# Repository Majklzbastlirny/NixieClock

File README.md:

# NixieClock (ESP-IDF firmware)

ESP-IDF + PlatformIO firmware for a 6-tube multiplexed nixie clock, replacing
the original ESPHome config (`nixieclock.yaml`, kept for reference). WiFi is used
for time sync and remote control; the clock keeps running (and keeps time, via
its RTC) with no network.

> **New here?** See **[GUIDE.md](GUIDE.md)** — a bilingual (English / Čeština)
> user guide with a *For everyone* section (setup, buttons, web page) and a
> *Power users* section (REST, MQTT/Home Assistant, building the firmware).

## Hardware

ESP32 (WROOM-32) on the **UCB32** controller board driving the
[**Unidisp**](https://github.com/Unipuls80/Unidisp) display board:

- Onboard UC3845 HV supply (~180 V, **no dimming input** → brightness is done in
  firmware by PWM-ing each tube's anode within its multiplex slot — the headline
  feature that wasn't possible under ESPHome).
- **MH74141** BCD cathode driver (old/slow Tesla part), **74×42** 1-of-10 anode
  multiplexer, 6× Z57xM/ZM1080 tubes. No per-digit decimal points — the only
  separator is the colon between the MM:SS pair.
- **PCF8563** RTC @ I²C 0x51 (driver also auto-detects DS1307/DS3231 @ 0x68).
- 5 front buttons on the multiplexed KEY line + a dedicated snooze button.
- Passive piezo buzzer on the ALM line (LEDC tone / RTTTL).
- Up to 2× **DS18B20** 1-Wire temperature sensors on GPIO13 (needs a 4.7 kΩ
  pull-up to 3.3 V).
- Optional **BH1750** ambient-light sensor on the shared I²C bus (address 0x23 or
  0x5C) — auto-detected at boot; enables light-driven night dimming when fitted.

Full pin map: [`components/common/include/pins.h`](components/common/include/pins.h).
Printable enclosure (case, bezel, panels, TPU feet) + print/assembly notes:
[`3D_Files/`](3D_Files/).

## Build & flash

Requires [PlatformIO](https://platformio.org/install) (CLI or the VS Code ext).

```sh
pio run                 # build
pio run -t upload       # build + flash over USB
pio device monitor      # serial console @ 115200
```

PlatformIO downloads the ESP-IDF 5.5 toolchain and the managed components
(`espressif/onewire_bus`, `espressif/ds18b20`) automatically on first build.
After changing a component's `idf_component.yml` or `REQUIRES`, do a clean
configure (`rm -rf .pio/build/esp32dev`) so the component manager re-runs.

> The board has **no auto-reset**: hold IO0, tap EN, release IO0 to enter
> download mode before `pio run -t upload`.

### Over-the-air (OTA) updates

The flash is a dual-OTA layout (two ~1.875 MB app slots + `otadata`), so after the
**first** serial flash you can update firmware over WiFi and never cable the clock
again:

1. `pio run` to build a new `.pio/build/esp32dev/firmware.bin`.
2. Open the clock's web UI (its IP is shown at the top of the page) → **Firmware**
   section → pick that `firmware.bin` → **Upload**.
3. It streams into the spare slot and reboots into it. The **Running** line shows the
   version and active slot (`ota_0`/`ota_1`), which flips after each successful update.

A failed or interrupted upload leaves the current firmware bootable — the new slot is
only made active once the whole image is written and verified. Settings and
WiFi/MQTT credentials live in NVS and are untouched by updates.

## First-time setup / credentials

Credentials live in NVS (set via the SoftAP portal or the web UI).
`components/common/include/secrets.h` (gitignored) is a **first-boot fallback
only**: once a WiFi SSID is stored in NVS the device trusts NVS exclusively (an
empty MQTT host means *no MQTT* — the client goes idle), and a factory reset
forces SoftAP setup on the next boot regardless of `secrets.h`.

To seed defaults at compile time, copy the template:

```sh
cp components/common/include/secrets.example.h components/common/include/secrets.h
# edit WIFI_SSID / WIFI_PASS / MQTT_* 
```

Or skip `secrets.h` entirely and provision over WiFi (see below).

## WiFi provisioning (SoftAP)

To set credentials without editing code (e.g. when lending the clock):

1. **Enter provisioning** — hold the provision button (button 5) during the
   boot window, or long-hold it (~3 s) during normal operation; it reboots into
   setup mode. (A board with no stored creds and no fallback SSID enters it
   automatically.)
2. The tubes show an **8-digit PIN** in two halves (colon lit = first half).
   Join the open-looking `NixieClock-XXXXXX` WiFi using that PIN as the WPA2
   password — so only someone looking at the clock can connect.
3. A captive portal opens: pick your network, enter the password (and optionally
   MQTT settings), save. The clock stores the creds and reboots onto your LAN.

WiFi/MQTT can also be changed live from the web UI's **Network** section (MQTT
applies immediately; WiFi on next reboot).

## Buttons

| Button | Short press | Long hold |
|--------|-------------|-----------|
| 1 | Brightness up | — |
| 2 | Brightness down | — |
| 3 | Show temperature now | — |
| 4 | Anti-poison scrub now | — |
| 5 (provision) | Show IP address on tubes | ~3 s: provisioning · ~10 s: factory reset |
| Snooze | Snooze ringing alarm | Dismiss alarm (until tomorrow) |

Bonus combo: **hold brightness + and − together (~2 s)** toggles the alarm on/off.

## Control surfaces

All three share one settings store, so changes from any surface are reflected
everywhere instantly:

- **Web UI** — `http://<clock-ip>/` : brightness, night schedule, anti-poison
  (interval, length, speed, 5 animations + mix, pause-for-interludes),
  alarm (incl. day-of-week + melody + snooze), temperature slots/decimals, and
  network config. Tap button 5 to see the IP on the tubes.
- **MQTT + Home Assistant** — auto-discovers as a *Nixie Clock* device
  (`nixie-<mac>`). Topics under `nixieclock/<node>/…`, HA discovery under
  `homeassistant/…`.
- **REST/JSON** — `GET /api/state`, `POST /api/set?k=<key>` (value in body) or
  the `GET /api/set?k=…&v=…` alias, `POST|GET /api/action?a=<action>`,
  `GET|POST /api/settime?epoch=…&tz=…` (set the clock from a client),
  `GET /api/net`, `POST /api/netset`, `POST /api/ota` (firmware upload),
  `GET /api/log`, `GET /api/blescan`, `GET /api/shellytime`.

## Features

- Smooth multiplex PWM brightness, ghost-free (cathode-before-anode + dead-time).
- SNTP timekeeping (configurable POSIX timezone), seeded from and written back to
  the RTC. Off-grid you can **set the clock from a phone/PC** — the web page and
  the SoftAP setup portal both send the device's time (and timezone), no NTP
  needed. The time is also saved to flash every few hours, so a power-lost RTC
  boots to an approximate time instead of 1970.
- Optional **Shelly BLE time**: Gen2+ Shellies (fw 2.x) acting as BLE gateways
  broadcast a time beacon (the one the Shelly BLU H&T Display syncs from), which
  the existing BLE scan picks up.
  - **Sync from Shelly now** button (web / HA / `shelly_sync` action).
  - Optional **daily** sync (`shelly_time_daily`), which yields to NTP: it only
    acts when SNTP hasn't synced for 24 h.
  - Takes the median of the Shellies heard, compensated for their 0–3 s burst lag.
    Expect about ±1 s accuracy, because the beacon carries whole seconds.
  - Debug panel / `GET /api/shellytime` lists each sender with its offset from
    the clock.
- Manual brightness + night dimming with three selectable modes: a **fixed**
  clock-time window (default 20:30→06:00), **sunrise/sunset** computed on-device
  from a configurable lat/lon (fully offline — no network needed), or **ambient
  light** from an optional BH1750 sensor (auto-detected at boot on I²C 0x23/0x5C;
  the light-driven mode is offered only when the sensor is present).
- Anti-cathode-poisoning cycle (periodic + on-demand).
- Two temperature slots + a **date** shown as brief interludes near the end of
  each minute — each interlude's **start second and duration are configurable**
  (defaults temp1 :53, temp2 :55, date :57). Temps are fed by MQTT, a DS18B20, or
  a **Shelly BLU H&T** read directly over BLE (passive BTHome v2 scan — no
  hub/gateway/cloud, picked from a live list in the web UI; press the sensor's
  button to highlight it, and its battery level shows with a low-battery cue — a
  colon blink); a per-slot calibration offset (°C); configurable decimals;
  negatives shown by blinking (no minus glyph), colon as decimal point. The date
  reads `DDMM : DoW` (day, month, then the ISO weekday after the colon). Night
  dimming in sun mode also takes a twilight offset (stay bright longer into
  dusk/dawn).
- Alarm with snooze + dismiss, day-of-week mask, and RTTTL melodies.
- Cold-start "slot machine" animation until the time is known.
- **Over-the-air updates** — upload a new `firmware.bin` from the web UI (dual-OTA
  slots); no serial needed after the first flash.
- **Web log viewer** — recent device log over `GET /api/log`, since the assembled
  clock has no serial access.

## Project layout

```
platformio.ini             build config (env: esp32dev), custom partition table
partitions.csv             dual-OTA: 2x ~1.875 MB app slots + otadata + NVS + SPIFFS (4 MB flash)
sdkconfig.defaults         ESP-IDF defaults
src/main.c                 app entry: orchestration + display draw loop
components/
  common/                  shared pin map + secrets (header-only)
  nixie/                   GPTimer multiplex display driver + PWM brightness
  i2cbus/                  shared I²C master + bus scanner
  rtcdev/                  RTC driver (PCF8563 / DS1307 / DS3231 auto-detect)
  netclock/                WiFi STA + SNTP
  netcfg/                  WiFi/MQTT credential store (NVS + secrets fallback)
  provision/               SoftAP captive-portal WiFi provisioning
  settings/                persisted settings blob (NVS) + change versioning
  control/                 shared key=value apply + state-JSON core
  mqttctrl/                MQTT client + Home Assistant autodiscovery
  webui/                   self-hosted web UI + REST/JSON API
  temps/                   temperature slots + DS18B20 (RMT 1-Wire)
  blescan/                 NimBLE passive scan → Shelly BLU H&T (BTHome v2)
  shellytime/              Shelly BLE time beacon → optional clock sync
  bh1750/                  optional ambient-light sensor (I²C) for lux night mode
  weblog/                  esp_log → RAM ring buffer, read over /api/log
  buttons/                 multiplexed-button debounce + classification
  alarm/                   alarm state machine
  buzzer/                  LEDC tone + RTTTL player
  antipoison/              anti-cathode-poisoning routine
```

Architecture note: `control` is the single place that maps a setting key=value
and renders the state JSON; MQTT, the web UI, and REST all go through it, so
adding a setting touches one switch and one JSON builder, not three.

## License

This project uses reciprocal ("share-alike") open licenses — you may use, copy,
and modify it, including commercially, but you must publish your modifications to
whichever part you change:

- **Firmware / source code** — [GNU GPL v3](LICENSE) (`LICENSE` at the repo root).
- **UCB32 controller board** (`PCB_Sources/ucb vibecheck_final/`) —
  [CERN-OHL-S v2](PCB_Sources/ucb%20vibecheck_final/LICENSE.txt) (CERN Open
  Hardware Licence, Strongly Reciprocal).

Third-party content keeps its own license: the **Unidisp** display board
(`PCB_Sources/Unidisp-main/`) is licensed by its author under CERN-OHL-W (Weakly
Reciprocal) — see its bundled `LICENSE`. The original ESPHome reference
(`nixieclock.yaml`) is retained only for reference.

## Credits

This started as a university project. The **Unidisp** digitron display board —
the HV supply, multiplexing, and tube driving — is the work of
[**@Unipuls80**](https://github.com/Unipuls80), along with his original
[Unidisp](https://github.com/Unipuls80/Unidisp) and an
[MH106 ASIC-based controller (ucb106)](https://github.com/Unipuls80/ucb106).

The **UCB32** controller board and this ESP32 firmware are my "modern" take on
driving the same display — by **Michal Basler** ([@Majklzbastlirny](https://github.com/Majklzbastlirny)).

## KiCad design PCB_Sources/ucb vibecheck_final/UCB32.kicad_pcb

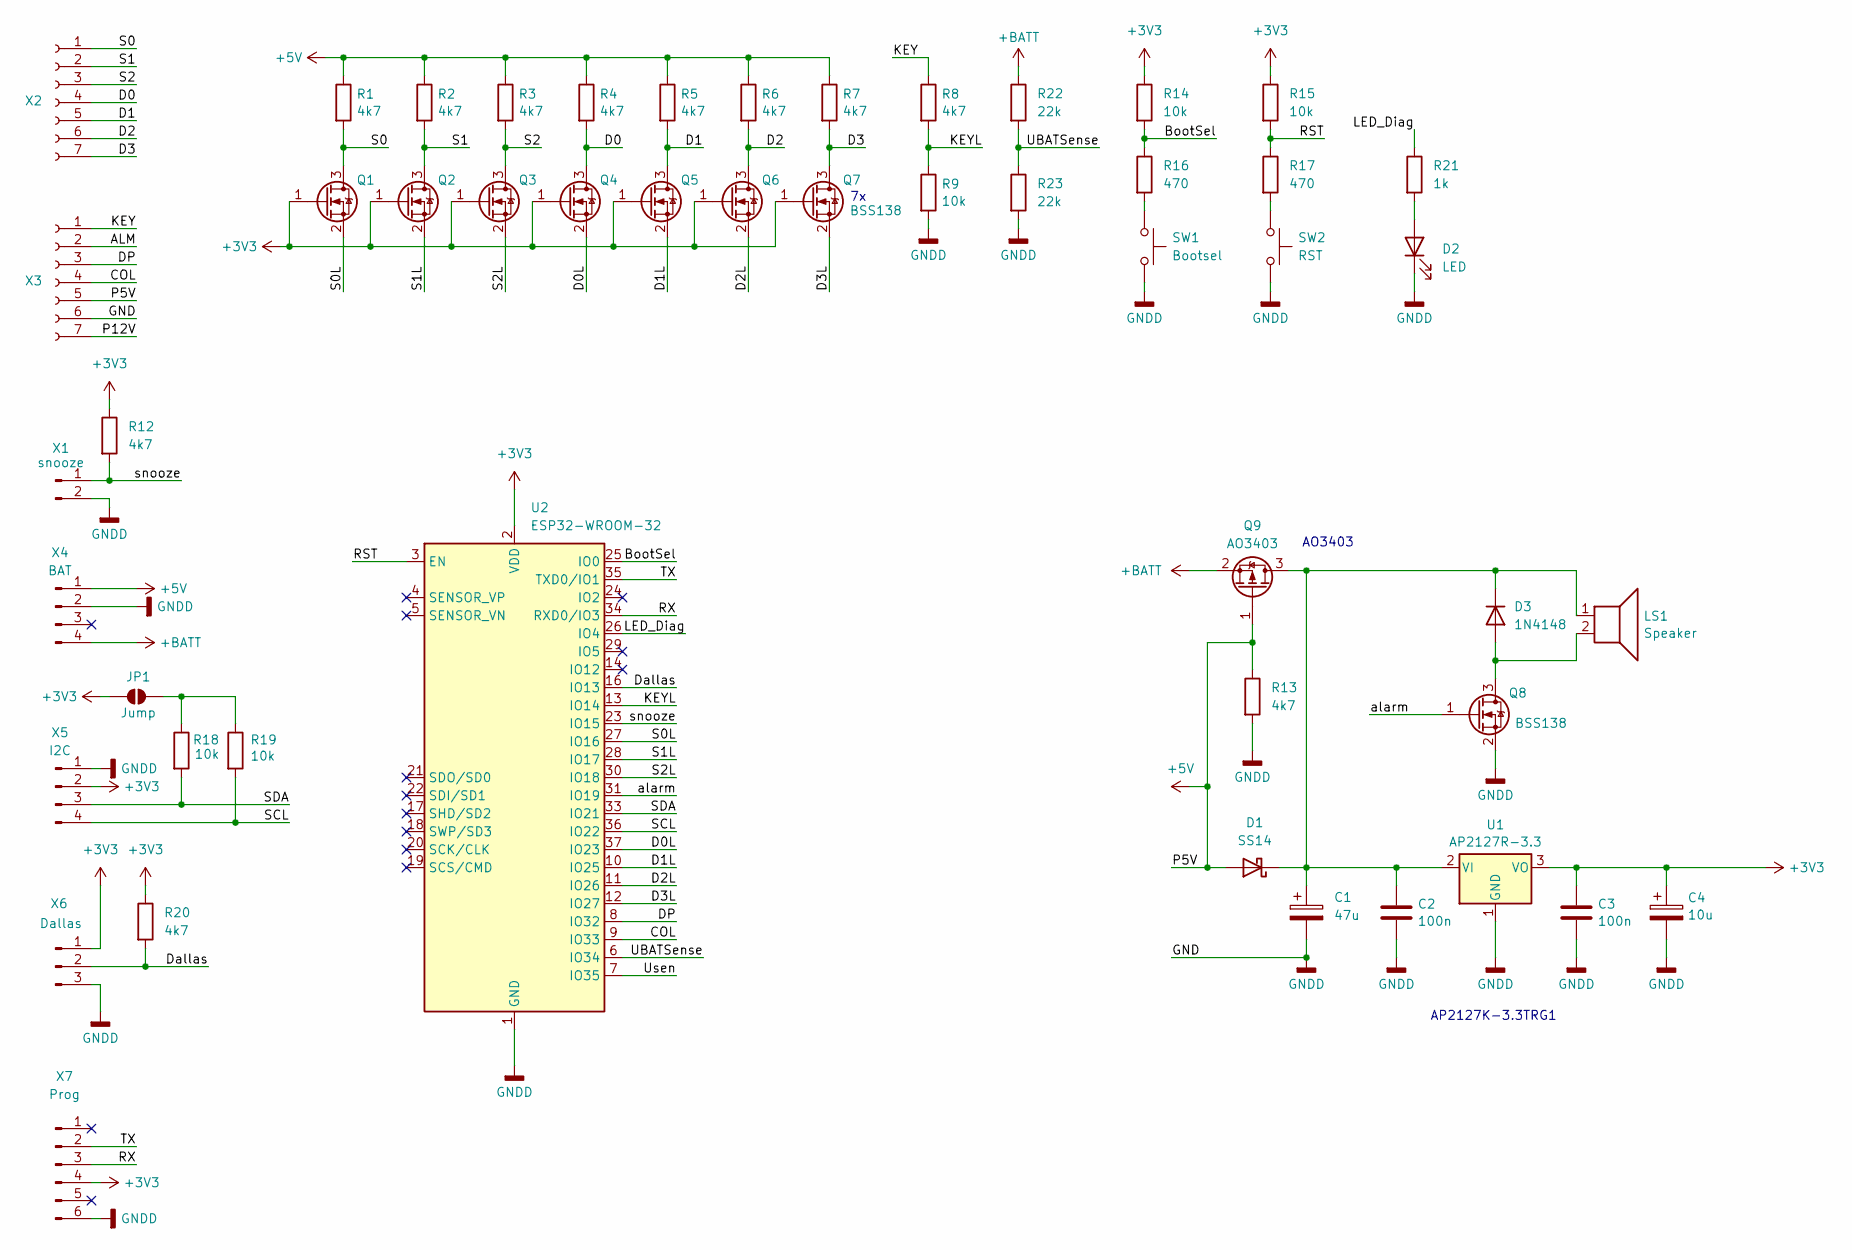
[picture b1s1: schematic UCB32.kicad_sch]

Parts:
C1: 47u; C_0805_2012Metric_Pad1.18x1.45mm_HandSolder
C2, C3: 100n; C_0805_2012Metric_Pad1.18x1.45mm_HandSolder
C4: 10u; C_0805_2012Metric_Pad1.18x1.45mm_HandSolder
D1: SS14; D_SMA
D2: LED; LED_0805_2012Metric_Pad1.15x1.40mm_HandSolder
D3: 1N4148; D_MiniMELF
JP1: Jump; SolderJumper-2_P1.3mm_Open_TrianglePad1.0x1.5mm
LS1: Speaker; Buzzer_TDK_PS1240P02BT_D12.2mm_H6.5mm
Q1, Q2, Q3, Q4, Q5, Q6, Q7, Q8: BSS138; SOT-23
Q9: AO3403; SOT-23
R1, R2, R3, R4, R5, R6, R7, R8, R12, R13, R20: 4k7; R_0805_2012Metric_Pad1.20x1.40mm_HandSolder
R9, R14, R15, R18, R19: 10k; R_0805_2012Metric_Pad1.20x1.40mm_HandSolder
R16, R17: 470; R_0805_2012Metric_Pad1.20x1.40mm_HandSolder
R21: 1k; R_0805_2012Metric_Pad1.20x1.40mm_HandSolder
R22, R23: 22k; R_0805_2012Metric_Pad1.20x1.40mm_HandSolder
SW1: Bootsel; SW_SPST_CK_RS282G05A3
SW2: RST; SW_SPST_CK_RS282G05A3
U1: AP2127R-3.3; SOT-89-3
U2: ESP32-WROOM-32
X1: snooze; PinHeader_1x02_P2.54mm_Vertical
X2, X3: Conn_01x07_Socket; PinSocket_1x07_P2.54mm_Vertical
X4: BAT; JST_XH_B4B-XH-A_1x04_P2.50mm_Vertical
X5: I2C; PinHeader_1x04_P2.54mm_Vertical
X6: Dallas; PinHeader_1x03_P2.54mm_Vertical
X7: Prog; PinSocket_1x06_P2.54mm_Vertical

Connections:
+3V3: C3.1, C4.1, JP1.1 (A), Q1.1 (G), Q2.1 (G), Q3.1 (G), Q4.1 (G), Q5.1 (G), Q6.1 (G), Q7.1 (G), R12.1, R14.1, R15.1, R20.1, U1.3 (VO), U2.2 (VDD), X5.2, X6.1, X7.4
+5V: D1.2 (A), Q9.1 (G), R1.1, R2.1, R3.1, R4.1, R5.1, R6.1, R7.1, R13.1, X3.5, X4.1
+BATT: Q9.2 (S), R22.1, X4.4
/ALM: X3.2
/BootSel: R14.2, R16.1, U2.25 (IO0)
/COL: U2.9 (IO33), X3.4
/D0: Q4.3 (D), R4.2, X2.4
/D0L: Q4.2 (S), U2.37 (IO23)
/D1: Q5.3 (D), R5.2, X2.5
/D1L: Q5.2 (S), U2.10 (IO25)
/D2: Q6.3 (D), R6.2, X2.6
/D2L: Q6.2 (S), U2.11 (IO26)
/D3: Q7.3 (D), R7.2, X2.7
/D3L: Q7.2 (S), U2.12 (IO27)
/DP: U2.8 (IO32), X3.3
/Dallas: R20.2, U2.16 (IO13), X6.2
/KEY: R8.1, X3.1
/KEYL: R8.2, R9.1, U2.13 (IO14)
/LED_Diag: R21.1, U2.26 (IO4)
/P12V: X3.7
/RST: R15.2, R17.1, U2.3 (EN)
/RX: U2.34 (RXD0/IO3), X7.3
/S0: Q1.3 (D), R1.2, X2.1
/S0L: Q1.2 (S), U2.27 (IO16)
/S1: Q2.3 (D), R2.2, X2.2
/S1L: Q2.2 (S), U2.28 (IO17)
/S2: Q3.3 (D), R3.2, X2.3
/S2L: Q3.2 (S), U2.30 (IO18)
/SCL: R19.2, U2.36 (IO22), X5.4
/SDA: R18.2, U2.33 (IO21), X5.3
/TX: U2.35 (TXD0/IO1), X7.2
/UBATSense: R22.2, R23.1, U2.6 (IO34)
/Usen: U2.7 (IO35)
/alarm: Q8.1 (G), U2.31 (IO19)
/snooze: R12.2, U2.23 (IO15), X1.1
GNDD: C1.2, C2.2, C3.2, C4.2, D2.1 (K), Q8.2 (S), R9.2, R13.2, R23.2, SW1.2, SW2.2, U1.1 (GND), U2.1 (GND), U2.15 (GND), U2.38 (GND), U2.39 (GND), X1.2, X3.6, X4.2, X5.1, X6.3, X7.6
unnamed: C1.1, C2.1, D1.1 (K), D3.1 (K), LS1.1, Q9.3 (D), U1.2 (VI)
unnamed: D2.2 (A), R21.2
unnamed: D3.2 (A), LS1.2, Q8.3 (D)
unnamed: JP1.2 (B), R18.1, R19.1
unnamed: R16.2, SW1.1
unnamed: R17.2, SW2.1

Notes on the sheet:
AO3403
AP2127K-3.3TRG1

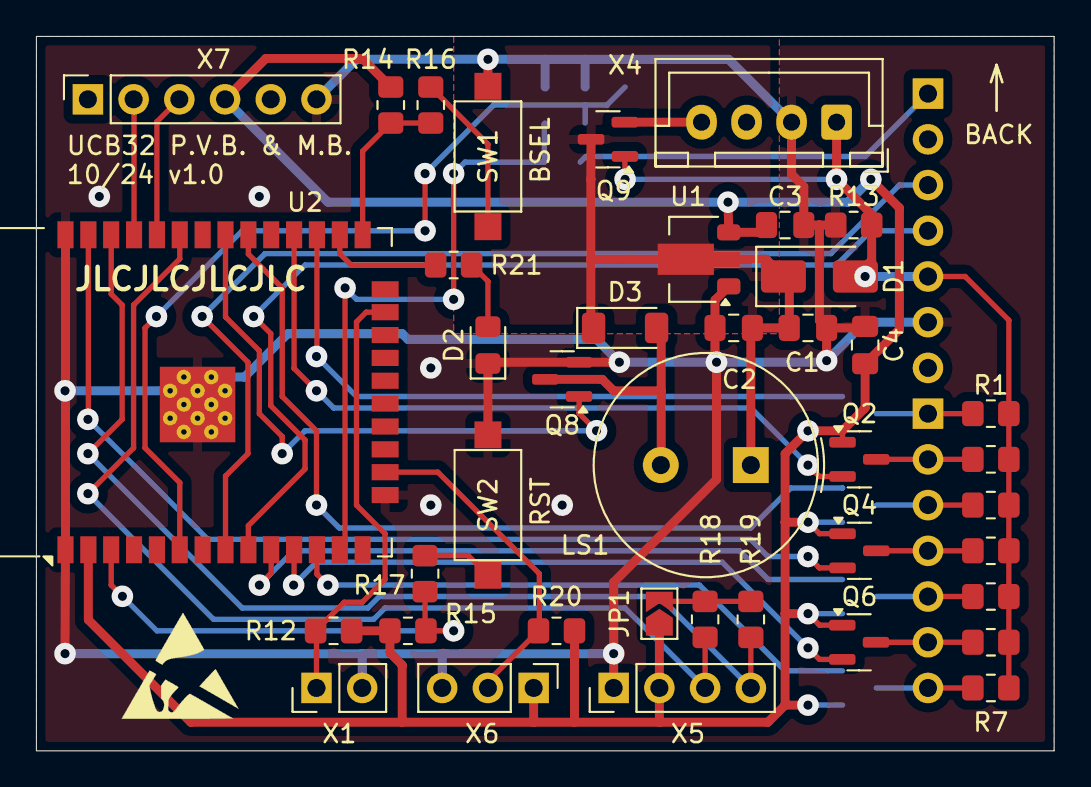
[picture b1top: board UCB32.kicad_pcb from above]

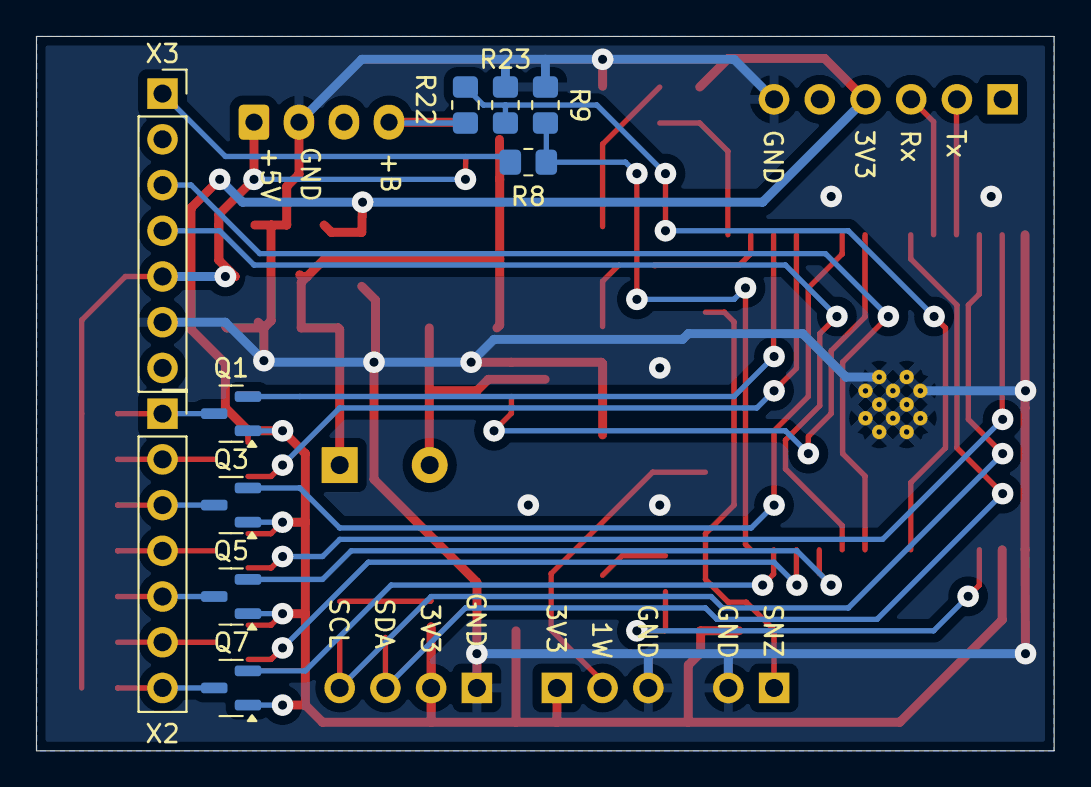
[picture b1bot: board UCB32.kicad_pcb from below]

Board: 2 copper layers, 56.5 x 39.7 mm, 50 parts (10 on the bottom side), 39 nets.

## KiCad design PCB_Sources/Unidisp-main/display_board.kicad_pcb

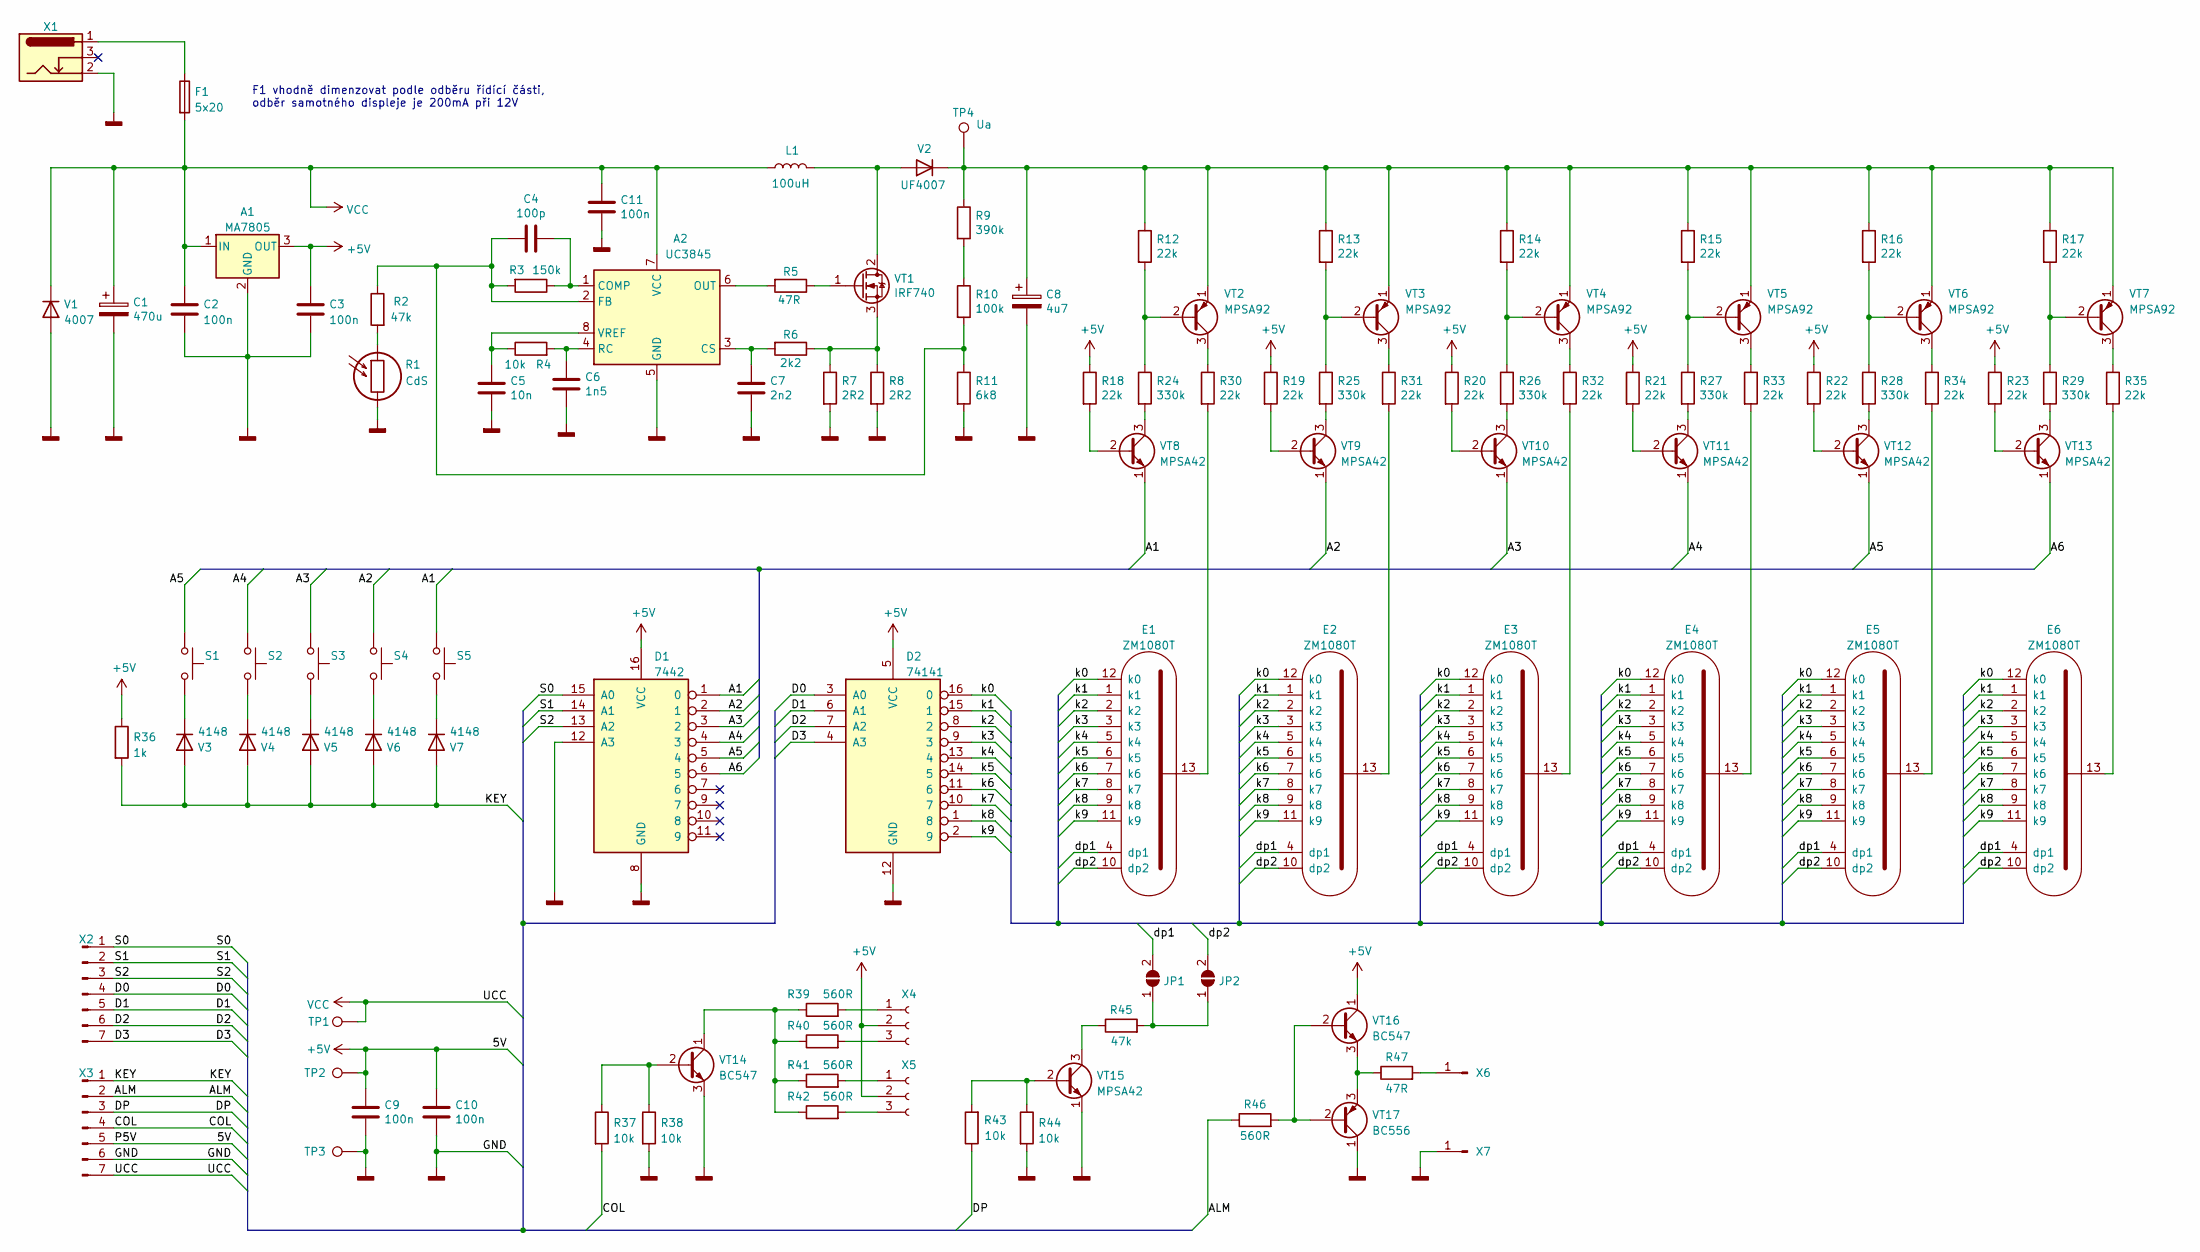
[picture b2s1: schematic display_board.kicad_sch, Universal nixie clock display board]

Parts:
A1: MA7805; TO-3_78xx
A2: UC3845; DIP-8_W7.62mm
C1: 470u; CP_Radial_D8.0mm_P3.80mm
C2, C3, C9, C10, C11: 100n; C_Disc_D4.3mm_W1.9mm_P5.00mm
C4: 100p; C_Disc_D4.3mm_W1.9mm_P5.00mm
C5: 10n; C_Disc_D4.3mm_W1.9mm_P5.00mm
C6: 1n5; C_Disc_D4.3mm_W1.9mm_P5.00mm
C7: 2n2; C_Disc_D4.3mm_W1.9mm_P5.00mm
C8: 4u7; CP_Radial_D10.0mm_P3.80mm
D1: 7442; DIP-16_W7.62mm
D2: 74141; DIP-16_W7.62mm
E1, E2, E3, E4, E5, E6: ZM1080T; nixie_13pin
F1: 5x20; Fuseholder_Cylinder-5x20mm_Stelvio-Kontek_PTF76_Horizontal_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
JP1, JP2: SolderJumper_2_Open; SolderJumper-2_P1.3mm_Open_Pad1.0x1.5mm
L1: 100uH; L_Radial_D8.7mm_P5.00mm_Fastron_07HCP
R1: CdS; R_LDR_D6.4mm_P3.4mm_Vertical
R2, R45: 47k; R DIN0207 10.16mm
R3: 150k; R DIN0207 10.16mm
R4, R37, R38, R43, R44: 10k; R DIN0207 10.16mm
R5, R47: 47R; R DIN0207 10.16mm
R6: 2k2; R DIN0207 10.16mm
R7, R8: 2R2; R DIN0207 10.16mm
R9: 390k; R DIN0207 10.16mm
R10: 100k; R DIN0207 10.16mm
R11: 6k8; R DIN0207 10.16mm
R12, R13, R14, R15, R16, R17, R18, R19, R20, R21, R22, R23, R30, R31, R32, R33, R34, R35: 22k; R DIN0207 10.16mm
R24, R25, R26, R27, R28, R29: 330k; R DIN0207 10.16mm
R36: 1k; R DIN0207 10.16mm
R39, R40, R41, R42, R46: 560R; R DIN0207 10.16mm
S1, S2, S3, S4, S5: SW_Push; SW_Tactile_SPST_Angled_PTS645Vx58-2LFS
TP1: Vcc; TestPoint_THTPad_D3.0mm_Drill1.5mm
TP2: +5V; TestPoint_THTPad_D3.0mm_Drill1.5mm
TP3: GND; TestPoint_THTPad_D3.0mm_Drill1.5mm
TP4: Ua; TestPoint_THTPad_D3.0mm_Drill1.5mm
V1: 4007; D_DO-41_SOD81_P10.16mm_Horizontal
V2: UF4007; D_DO-41_SOD81_P10.16mm_Horizontal
V3, V4, V5, V6, V7: 4148; D_DO-35_SOD27_P10.16mm_Horizontal
VT1: IRF740; TO-220-3_Horizontal_TabDown
VT2, VT3, VT4, VT5, VT6, VT7: MPSA92; TO-92_Wide
VT8, VT9, VT10, VT11, VT12, VT13, VT15: MPSA42; TO-92_Wide
VT14, VT16: BC547; TO-92_Wide
VT17: BC556; TO-92_Wide
X1: Barrel_Jack_Switch; BarrelJack_Horizontal
X2, X3: Conn_01x07_Male; PinHeader_1x07_P2.54mm_Vertical
X4, X5: Conn_01x03_Female; PinSocket_1x03_P2.54mm_Vertical
X6, X7: Conn_01x01_Male; PinHeader_1x01_P2.54mm_Vertical

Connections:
+5V: A1.3 (OUT), C3.1, C9.1, C10.1, D1.16 (VCC), D2.5 (VCC), R18.1, R19.1, R20.1, R21.1, R22.1, R23.1, R36.1, TP2.1, VT16.1 (C), X3.5, X4.2, X5.2
/A1: D1.1 (0), S5.1, VT8.1 (E)
/A2: D1.2 (1), S4.1, VT9.1 (E)
/A3: D1.3 (2), S3.1, VT10.1 (E)
/A4: D1.4 (3), S2.1, VT11.1 (E)
/A5: D1.5 (4), S1.1, VT12.1 (E)
/A6: D1.6 (5), VT13.1 (E)
/ALM: R46.1, X3.2
/COL: R37.2, X3.4
/D0: D2.3 (A0), X2.4
/D1: D2.6 (A1), X2.5
/D2: D2.7 (A2), X2.6
/D3: D2.4 (A3), X2.7
/DP: R43.1, X3.3
/KEY: R36.2, V3.2 (A), V4.2 (A), V5.2 (A), V6.2 (A), V7.2 (A), X3.1
/S0: D1.15 (A0), X2.1
/S1: D1.14 (A1), X2.2
/S2: D1.13 (A2), X2.3
/dp1: E1.4 (dp1), E2.4 (dp1), E3.4 (dp1), E4.4 (dp1), E5.4 (dp1), E6.4 (dp1), JP1.2 (B)
/dp2: E1.10 (dp2), E2.10 (dp2), E3.10 (dp2), E4.10 (dp2), E5.10 (dp2), E6.10 (dp2), JP2.2 (B)
/k0: D2.16 (0), E1.12 (k0), E2.12 (k0), E3.12 (k0), E4.12 (k0), E5.12 (k0), E6.12 (k0)
/k1: D2.15 (1), E1.1 (k1), E2.1 (k1), E3.1 (k1), E4.1 (k1), E5.1 (k1), E6.1 (k1)
/k2: D2.8 (2), E1.2 (k2), E2.2 (k2), E3.2 (k2), E4.2 (k2), E5.2 (k2), E6.2 (k2)
/k3: D2.9 (3), E1.3 (k3), E2.3 (k3), E3.3 (k3), E4.3 (k3), E5.3 (k3), E6.3 (k3)
/k4: D2.13 (4), E1.5 (k4), E2.5 (k4), E3.5 (k4), E4.5 (k4), E5.5 (k4), E6.5 (k4)
/k5: D2.14 (5), E1.6 (k5), E2.6 (k5), E3.6 (k5), E4.6 (k5), E5.6 (k5), E6.6 (k5)
/k6: D2.11 (6), E1.7 (k6), E2.7 (k6), E3.7 (k6), E4.7 (k6), E5.7 (k6), E6.7 (k6)
/k7: D2.10 (7), E1.8 (k7), E2.8 (k7), E3.8 (k7), E4.8 (k7), E5.8 (k7), E6.8 (k7)
/k8: D2.1 (8), E1.9 (k8), E2.9 (k8), E3.9 (k8), E4.9 (k8), E5.9 (k8), E6.9 (k8)
/k9: D2.2 (9), E1.11 (k9), E2.11 (k9), E3.11 (k9), E4.11 (k9), E5.11 (k9), E6.11 (k9)
GNDD: A1.2 (GND), A2.5 (GND), C1.2, C2.2, C3.2, C5.2, C6.2, C7.2, C8.2, C9.2, C10.2, C11.2, D1.8 (GND), D1.12 (A3), D2.12 (GND), R1.2, R7.2, R8.2, R11.2, R38.2, R44.2, TP3.1, V1.2 (A), VT14.3 (E), VT15.1 (E), VT17.1 (C), X1.2, X3.6, X7.1
unnamed: A2.1 (COMP), C4.1, R3.1
unnamed: A2.2 (FB), C4.2, R2.1, R3.2, R10.2, R11.1
unnamed: A2.3 (CS), C7.1, R6.2
unnamed: A2.4 (RC), C6.1, R4.2
unnamed: A2.6 (OUT), R5.2
unnamed: A2.8 (VREF), C5.1, R4.1
unnamed: C8.1, R9.1, R12.1, R13.1, R14.1, R15.1, R16.1, R17.1, TP4.1, V2.1 (K), VT2.1 (E), VT3.1 (E), VT4.1 (E), VT5.1 (E), VT6.1 (E), VT7.1 (E)
unnamed: E1.13, R30.2
unnamed: E2.13, R31.2
unnamed: E3.13, R32.2
unnamed: E4.13, R33.2
unnamed: E5.13, R34.2
unnamed: E6.13, R35.2
unnamed: F1.1, X1.1
unnamed: JP1.1 (A), JP2.1 (A), R45.2
unnamed: L1.2, V2.2 (A), VT1.2 (D)
unnamed: R1.1, R2.2
unnamed: R5.1, VT1.1 (G)
unnamed: R6.1, R7.1, R8.1, VT1.3 (S)
unnamed: R9.2, R10.1
unnamed: R12.2, R24.1, VT2.2 (B)
unnamed: R13.2, R25.1, VT3.2 (B)
unnamed: R14.2, R26.1, VT4.2 (B)
unnamed: R15.2, R27.1, VT5.2 (B)
unnamed: R16.2, R28.1, VT6.2 (B)
unnamed: R17.2, R29.1, VT7.2 (B)
unnamed: R18.2, VT8.2 (B)
unnamed: R19.2, VT9.2 (B)
unnamed: R20.2, VT10.2 (B)
unnamed: R21.2, VT11.2 (B)
unnamed: R22.2, VT12.2 (B)
unnamed: R23.2, VT13.2 (B)
unnamed: R24.2, VT8.3 (C)
unnamed: R25.2, VT9.3 (C)
unnamed: R26.2, VT10.3 (C)
unnamed: R27.2, VT11.3 (C)
unnamed: R28.2, VT12.3 (C)
unnamed: R29.2, VT13.3 (C)
unnamed: R30.1, VT2.3 (C)
unnamed: R31.1, VT3.3 (C)
unnamed: R32.1, VT4.3 (C)
unnamed: R33.1, VT5.3 (C)
unnamed: R34.1, VT6.3 (C)
unnamed: R35.1, VT7.3 (C)
unnamed: R37.1, R38.1, VT14.2 (B)
unnamed: R39.1, R40.1, R41.1, R42.1, VT14.1 (C)
unnamed: R39.2, X4.1
unnamed: R40.2, X4.3
unnamed: R41.2, X5.1
unnamed: R42.2, X5.3
unnamed: R43.2, R44.1, VT15.2 (B)
unnamed: R45.1, VT15.3 (C)
unnamed: R46.2, VT16.2 (B), VT17.2 (B)
unnamed: R47.1, VT16.3 (E), VT17.3 (E)
unnamed: R47.2, X6.1
unnamed: S1.2, V3.1 (K)
unnamed: S2.2, V4.1 (K)
unnamed: S3.2, V5.1 (K)
unnamed: S4.2, V6.1 (K)
unnamed: S5.2, V7.1 (K)
VCC: A1.1 (IN), A2.7 (VCC), C1.1, C2.1, C11.1, F1.2, L1.1, TP1.1, V1.1 (K), X3.7

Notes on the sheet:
F1 vhodně dimenzovat podle odběru řídící části, odběr samotného displeje je 200mA při 12V

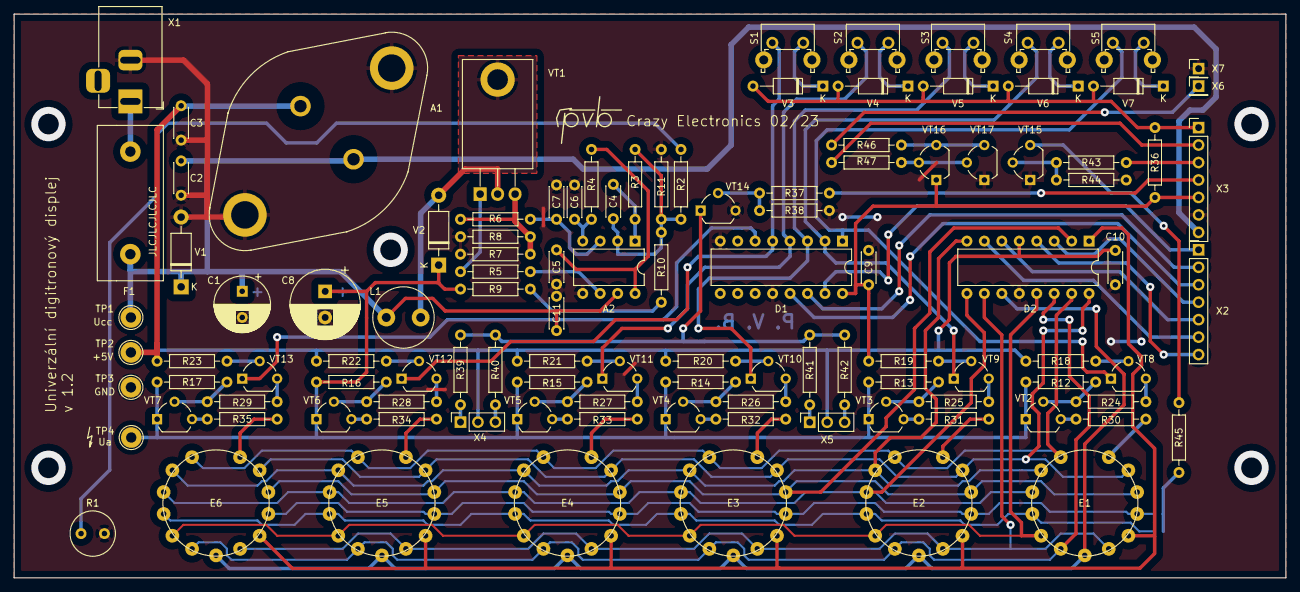
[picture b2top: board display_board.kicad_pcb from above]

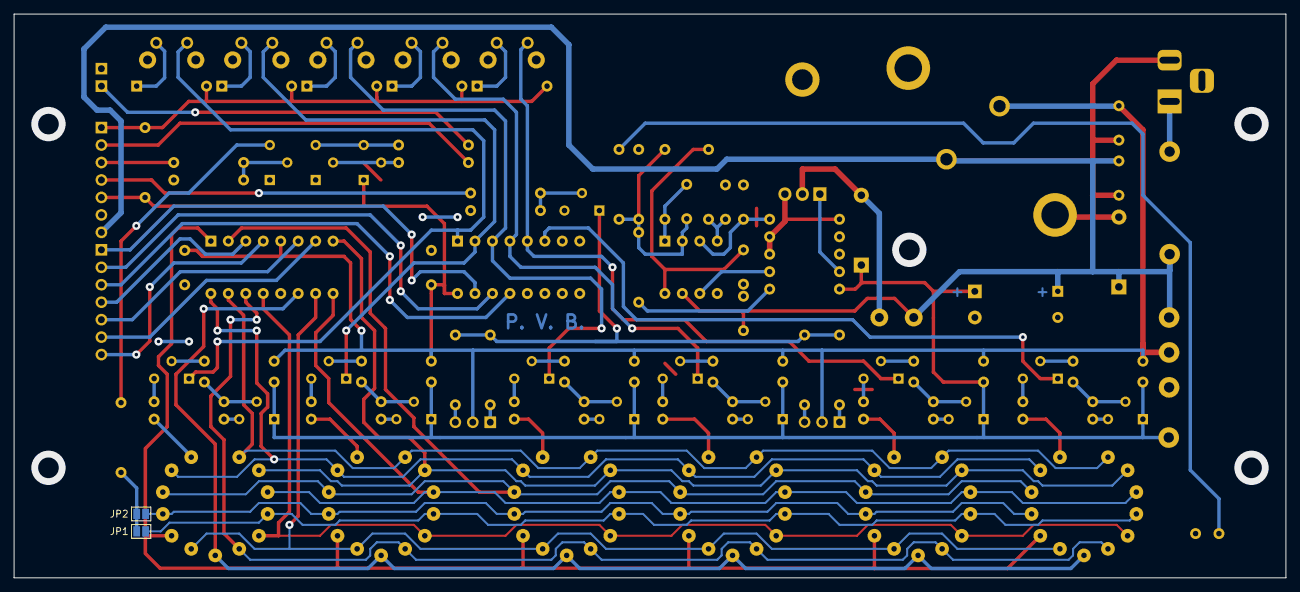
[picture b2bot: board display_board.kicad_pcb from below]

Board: 2 copper layers, 185.0 x 82.0 mm, 112 parts (2 on the bottom side), 92 nets.

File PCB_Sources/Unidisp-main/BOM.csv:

Indukčnosti;;
L1;100uH 2A pp. 50kHz;radiální
;;
Rezistory ;;
R1;CdS 5mm;-
R2, R45;47k 5% ;R0207
R3;150k 5% ;R0207
R4;10k 1%;R0207
R5, R47;47R 5%;R0207
R6;2k2 5%;R0207
R7, R8;2R2 5%;R0207
R9;390k 1%;R0207
R10;100k 1%;R0207
R11 ;6k8 1%;R0207
R12 .. R23;22k 5%;R0207
R30 .. R35;;
R24 .. R29;330k 5%;R0207
R36;1k 5%;R0207
R37, R38;10k 5%;R0207
R43, R44;;
R39 .. R42, R46;560R 5%;R0207
;;
Kondenzátory;;
C1;470uF 16V ;elektrol. radiální
C2, C3, C9;100n 16V;keramický
C10, C11;;
C4;100p 16V ;keramický
C5;10n 16V ;keramický
C6 ;1n5 16V ;keramický
C7;2n2 16V ;keramický
C8;4,7uF 250V ;elektrol. radiální
;;
Diody;;
V1;1N4007;-
V2;UF4007;-
V3..V7;1N4148;-
;;
Tranzistory;;
VT1;IRF740;upevnit k DPS
VT2..VT7;MPSA92;-
VT8..VT13, VT15;MPSA42;-
VT14, VT16;BC547 ;-
VT17;BC556 ;-
;;
Integrované obvody;;
A1;MA7805;upevnit k DPS
A2;UC3845;-
D1;74x42;-
D2;74x141;-
;;
Výbojky;;
E1..E6;Z57xM, ZM1080(T) a ekvivalentní;
;;
Konektory;;
X1;zdířka souosá;5,5mm/2,1mm
X2..X7;hřeben, samec;2,54mm
;;
Pojistky;;
F1;podle celk. odběru;5x20mm
pouzdro pro F1;PTF76 ;15mm rozteč

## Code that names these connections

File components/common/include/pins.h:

// Central pin map for the NixieClock (UCB32 controller + Unidisp display board).
//
// The display is a 6-tube, time-multiplexed nixie panel. One tube is lit at a
// time; the firmware walks through them fast enough to look continuous.
//
//   Tube select (74x42, "S0..S2" on the Unidisp X2 header):
//     code 0 = RIGHTMOST tube ... code 5 = LEFTMOST tube, code 6/7 = display off.
//   Digit value (MH74141, "D0..D3"): BCD. A value >= 10 (e.g. 0xF) blanks the
//     selected tube without disabling its anode — handy for per-tube dimming
//     while still reading that tube's multiplexed button.
//
// All Unidisp logic is 5V TTL but reads the ESP32's 3.3V output as logic high.
// KEY is open-drain active-low and idles high through the ESP's internal pullup.
#pragma once

#include "driver/gpio.h"

// --- Tube select (anode multiplex, 74x42 address) ---
#define PIN_SEL0        GPIO_NUM_16   // S0 / LSB
#define PIN_SEL1        GPIO_NUM_17   // S1
#define PIN_SEL2        GPIO_NUM_18   // S2 / MSB

// --- Digit value (cathode, MH74141 BCD) ---
#define PIN_BCD0        GPIO_NUM_23   // D0 / LSB
#define PIN_BCD1        GPIO_NUM_25   // D1
#define PIN_BCD2        GPIO_NUM_26   // D2
#define PIN_BCD3        GPIO_NUM_27   // D3 / MSB

// --- Decorations ---
#define PIN_DOT         GPIO_NUM_32   // DP: per-tube decimal points (multiplexed, H = on)
#define PIN_COLON       GPIO_NUM_33   // COL: the ':' separator LEDs (not multiplexed)

// --- Inputs ---
#define PIN_KEY         GPIO_NUM_14   // multiplexed front buttons, active-low, needs pullup
#define PIN_SNOOZE      GPIO_NUM_15   // snooze button, active-low

// --- Audio ---
#define PIN_BUZZER      GPIO_NUM_19   // ALM: passive piezo, driven via LEDC

// --- I2C bus (DS3231 RTC @ 0x68; future BH1750 light sensor @ 0x23) ---
#define PIN_I2C_SDA     GPIO_NUM_21
#define PIN_I2C_SCL     GPIO_NUM_22

// --- 1-Wire (DS18B20 temperature, RMT-driven) ---
#define PIN_ONEWIRE     GPIO_NUM_13   // needs a 4.7k pull-up to 3.3V on the data line

// --- Misc ---
#define PIN_STATUS_LED  GPIO_NUM_4
#define PIN_BATT_ADC    GPIO_NUM_34   // ADC1_CH6, 22k/22k divider (x2). Unused in v1.

#define NIXIE_NUM_TUBES 6
